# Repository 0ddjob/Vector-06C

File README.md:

# Vector 06C
Information about the 8080 based computer from the Moldovan SSR.<br>

This information covers the 2nd model ... Вектор 06Ц.02 ... which doesn't seem well documented in English.<br>

More information about the original model, including software, can be found on [this](https://github.com/alemorf/retro_computers/tree/master/Vector_06C) repository.<br>

## [Vector 06C.02](/Vector-06C-02)
Information about the 2nd version of the 06C, including [schematics](/Vector-06C-02/Schematics), [video output](/Vector-06C-02/Video_Sync), [power](/Vector-06C-02/Power), etc.<br>

## [Powering](/Vector-06C-02/Power)
As the Vector is an 8080-based computer it requires ±5VDC and +12VDC to run.  This describes one way to power the Vector if you don't have, or trust, the original tri-voltage power supply.

## [Utilities](/Utils/ROM2WAV)
Terminal utility to covert ROM/BIN software to WAV format, compiled for MacOS 15.5.

## [WAV Files](/Software_WAV)
Software for the Vector that can be loaded "from tape".

## My Vector

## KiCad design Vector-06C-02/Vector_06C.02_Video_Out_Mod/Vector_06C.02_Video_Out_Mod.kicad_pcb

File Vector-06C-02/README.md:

# Вектор 06Ц.02/Vector 06C.02
## Connector Pinouts

### XS1 "ВУ" System Bus
This is a 3x45 connector of type СНП34С-90/132х9,4Р-22 where the middle "B" row is not connected.

### XS2 "ПУ" Printer Port
This is a 3x10 connector of type СНП34С-30/27х9,4Р-22.  All three rows are connected.

### XS3 "J1" & XS4 "J2"
Joystick 1 & 2 connections, 7-pin DIN sockets.<br>
|Цель|-<|Eng|
|---|---|---|
|1|Верх|Up|
|2|0V|Ground|
|3|Право|Right|
|4|Наз (?)|Down|
|5|Кн. 2|Button 2|
|6|Лево|Left|
|7|Кн. 1|Button 1|

### XS5 "RGB"
7-pin DIN socket.
|Цель|-<|Eng|
|---|---|---|
|1|Збук|Sound|
|2|Видео|Composite Video|
|3|B|Blue|
|4|G|Green|
|5|R|Red|
|6|0V|Ground|
|7|Упров|Control|

Pin 2 appears to be composite video and thus can be used for C.SYNC.<br>
Pin 7 is connected to +12V so likely used for SCART control.<br>

### XS6 "O__O" Магнетофон/Cassette
5-pin DIN socket, you can use a 3-pin or 5-pin DIN plug.
|Цель|-<|Eng|
|---|---|---|
|1|Выход|Mic|
|2|0V|Ground|
|3|Вход|Ear|
|4|x|x|
|5|x|x|

### XS7 "CTV"
This three pin connector appears to control whether the RGB signal is inverted or not.  The "target" (Цель) could be the type of RGB decoder (?): MC-3 or MC-31.<br>

From the schematic:
|Цель|-<|
|---|---|
|МЦ-3|1|
|П/?|2|
|МЦ-31|3|

Pin 1 = ground<br>
Pin 2 = XOR input on D61 & D67<br>
Pin 3 = no connection (pin 2 is pulled up to +5V)<br>

D61 & D67 are КР1533ЛП5 (74ALS86) which are quad two-input XOR gates.<br>

The functionality is that when 1-2 are bridged then one input to the XOR gates is low, meaning the RGB signal is not affected: RGB low remains low, RGB high remains high.<br>
If 2-3 are bridged then one input is high which inverts the RGB signal: if RGB is low then it becomes high, and high becomes low.<br>

### XS8 "Power"
7-pin DIN socket.
|Цель|-<|
|---|---|
|1|0V/Ground|
|2|-5V|
|3|+5V|
|4|-5V|
|5|+12V|
|6|0V/Ground|
|7|+5V|

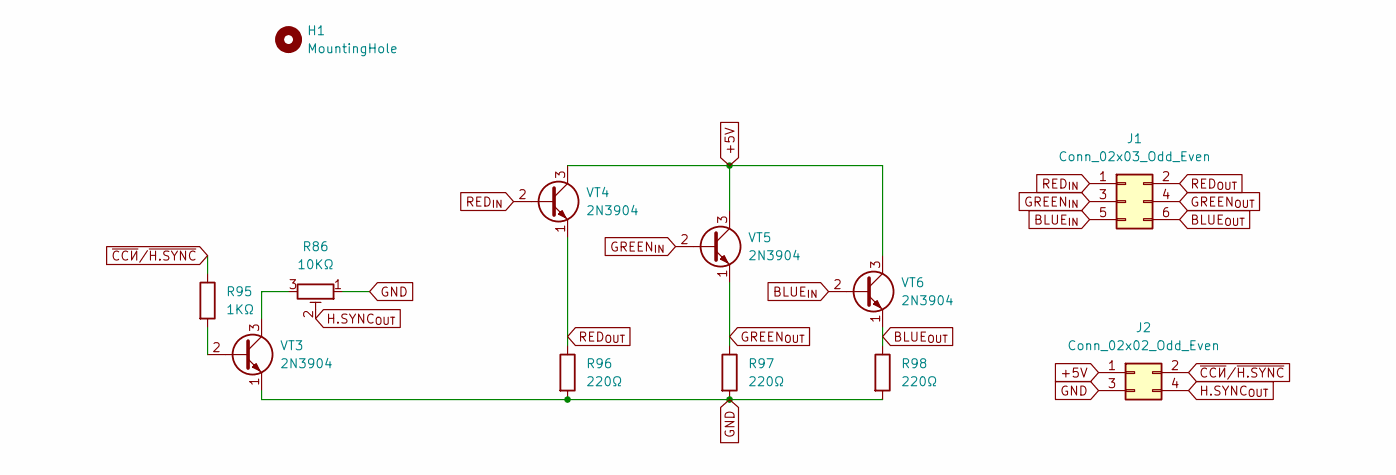
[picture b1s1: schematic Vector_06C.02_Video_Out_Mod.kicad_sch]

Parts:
H1: MountingHole; MountingHole_3.2mm_M3
J1: Conn_02x03_Odd_Even; PinHeader_2x03_P2.54mm_Vertical
J2: Conn_02x02_Odd_Even; PinHeader_2x02_P2.54mm_Vertical
R86: 10KΩ; Potentiometer_Bourns_3266W_Vertical
R95: 1KΩ; R_Axial_DIN0207_L6.3mm_D2.5mm_P7.62mm_Horizontal
R96, R97, R98: 220Ω; R_Axial_DIN0207_L6.3mm_D2.5mm_P7.62mm_Horizontal
VT3, VT4, VT5, VT6: 2N3904; TO-92_Inline

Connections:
+5V: J2.1, VT4.3 (C), VT5.3 (C), VT6.3 (C)
BLUE_{IN}: J1.5, VT6.2 (B)
BLUE_{OUT}: J1.6, R98.1, VT6.1 (E)
GND: J2.3, R86.1, R96.2, R97.2, R98.2, VT3.1 (E)
GREEN_{IN}: J1.3, VT5.2 (B)
GREEN_{OUT}: J1.4, R97.1, VT5.1 (E)
H.SYNC_{OUT}: J2.4, R86.2
unnamed: R95.2, VT3.2 (B)
unnamed: R86.3, VT3.3 (C)
RED_{IN}: J1.1, VT4.2 (B)
RED_{OUT}: J1.2, R96.1, VT4.1 (E)
~ССИ/~H.SYNC: J2.2, R95.1

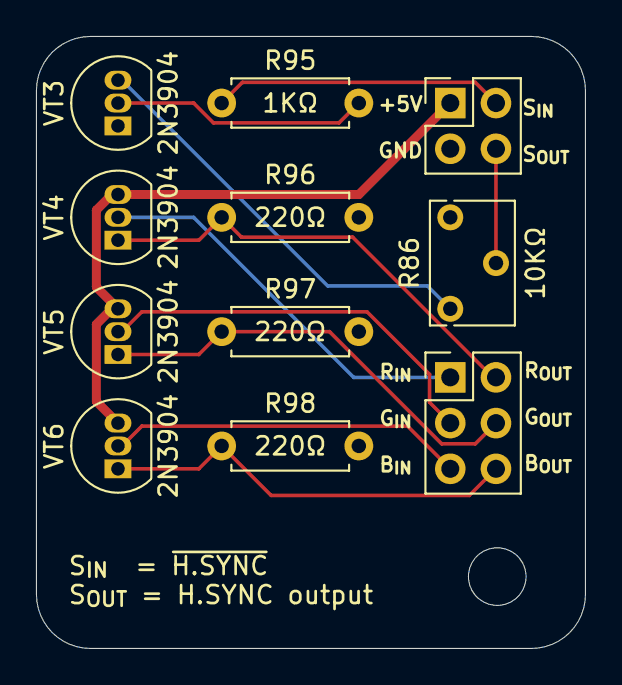
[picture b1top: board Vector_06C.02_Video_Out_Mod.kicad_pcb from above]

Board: 2 copper layers, 30.5 x 34.0 mm, 12 parts (0 on the bottom side), 12 nets.

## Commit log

2025-06-20 Additional files
2025-06-20 Added file extension for clarity
2025-06-20 Added datasheets
2025-06-21 New schemas
2025-09-16 Started drawing KiCad schematic
2025-09-29 Finalised video mod board design
2025-10-12 Corrected schematic
2025-10-12 Added motherboard modification photos
    PXD files are Pixelmator Pro (macOS)
